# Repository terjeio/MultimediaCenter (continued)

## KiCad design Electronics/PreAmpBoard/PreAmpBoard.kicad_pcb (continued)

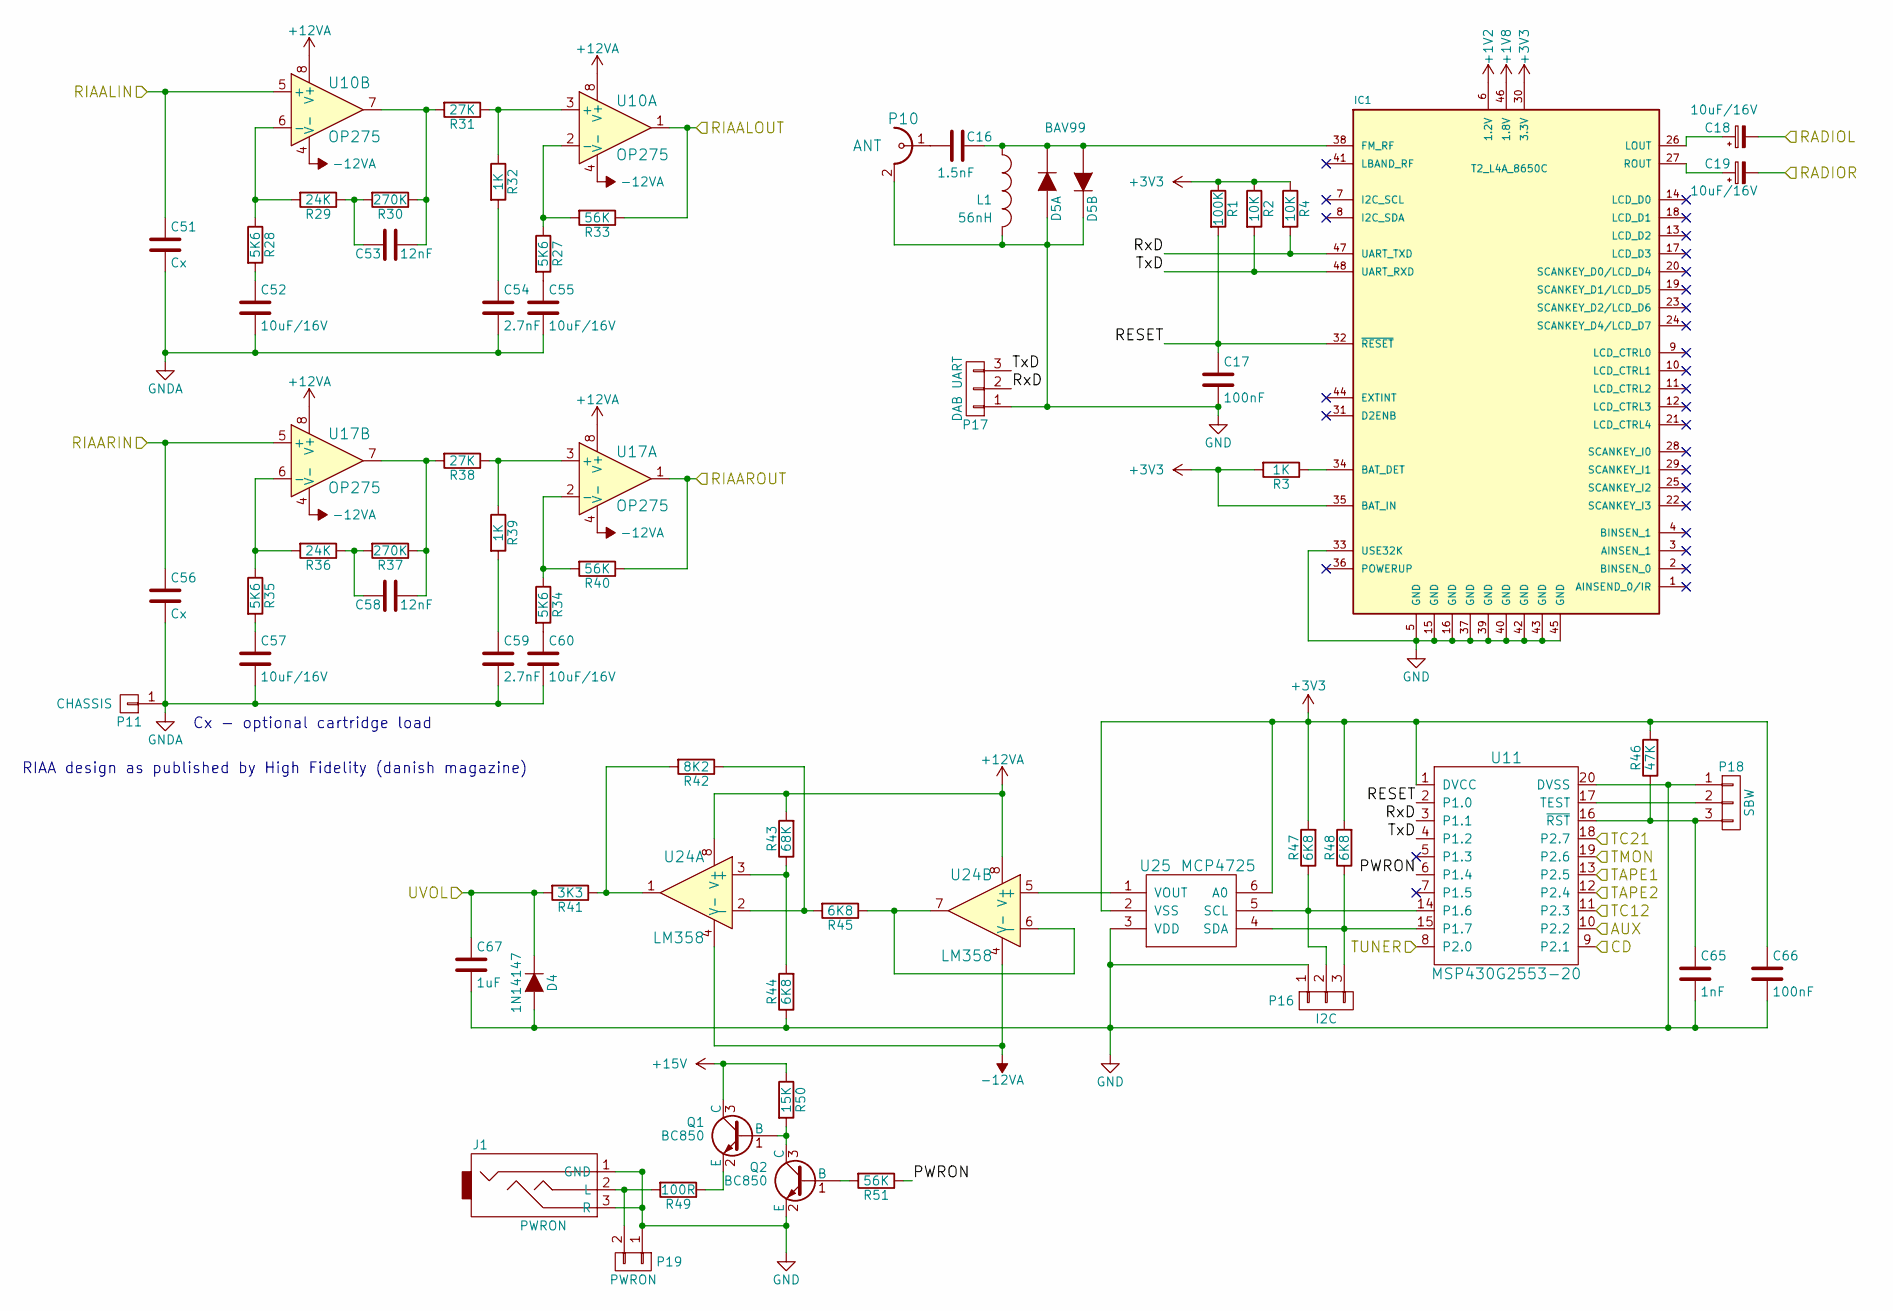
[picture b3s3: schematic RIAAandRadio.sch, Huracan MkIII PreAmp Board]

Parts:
C16: 1.5nF; C_0805
C17, C66: 100nF; C_1206
C18, C19: 10uF/16V; c_elec_3x5.3
C51, C56: Cx; C_Disc_D3_P5
C52, C55, C57, C60: 10uF/16V; C_Radial_D5_L11_P2.5
C53, C58: 12nF; C_Disc_D3_P5
C54, C59: 2.7nF; C_Disc_D3_P5
C65: 1nF; C_0805
C67: 1uF; C_1206
D4: 1N14147; SOD-123
D5: BAV99; SOT-23
IC1: T2_L4A_8650C; T2-L4A-8650C
J1: PWRON; PSG01538
L1: 56nH; R_0805
P10: ANT; CON-SMA-EDGE
P11: CHASSIS; Pin_Header_Straight_1x01
P16: I2C; 70543-03
P17: DAB UART; 70543-03
P18: SBW; Pin_Header_Straight_1x03
P19: PWRON; Pin_Header_Straight_1x02
Q1, Q2: BC850; SOT-23
R1: 100K; R_0805
R2, R4: 10K; R_0805
R3: 1K; R_0805
R27, R28, R34, R35: 5K6; Resistor_Horizontal_RM10mm
R29, R36: 24K; Resistor_Horizontal_RM10mm
R30, R37: 270K; Resistor_Horizontal_RM10mm
R31, R38: 27K; Resistor_Horizontal_RM10mm
R32, R39: 1K; Resistor_Horizontal_RM10mm
R33, R40: 56K; Resistor_Horizontal_RM10mm
R41: 3K3; R_0805
R42: 8K2; R_0805
R43: 68K; R_0805
R44, R45, R47, R48: 6K8; R_0805
R46: 47K; R_0805
R49: 100R; Resistor_Horizontal_RM10mm
R50: 15K; R_0805
R51: 56K; R_0805
U10, U17: OP275; DIP-8__300
U11: MSP430G2553-20; TSSOP20
U24: LM358; SO-8
U25: MCP4725; SOT23-6

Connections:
+1V2: IC1.6 (1.2V); also elsewhere on the board
+1V8: IC1.46 (1.8V); also elsewhere on the board
+3V3: C66.1, IC1.30 (3.3V), IC1.35 (BAT_IN), R1.1, R2.1, R3.2, R4.1, R46.2, R47.2, R48.2, U11.1 (DVCC), U25.2 (VSS), U25.6 (A0); also elsewhere on the board
+12VA: R43.2, U10.8 (V+), U17.8 (V+), U24.8 (V+); also elsewhere on the board
+15V: Q1.3 (C), R50.1
/AUX: U11.10 (P2.2); also elsewhere on the board
/CD: U11.9 (P2.1); also elsewhere on the board
/RADIOL: C18.2; also elsewhere on the board
/RADIOR: C19.2; also elsewhere on the board
/RIAA&Radio/PWRON: R51.1, U11.6 (P1.4)
/RIAA&Radio/RESET: C17.1, IC1.32 (~RESET), R1.2, U11.2 (P1.0)
/RIAA&Radio/RxD: IC1.47 (UART_TXD), P17.2, R4.2, U11.3 (P1.1)
/RIAA&Radio/TxD: IC1.48 (UART_RXD), P17.3, R2.2, U11.4 (P1.2)
/RIAALIN: C51.1, U10.5 (+); also elsewhere on the board
/RIAALOUT: R33.1, U10.1; also elsewhere on the board
/RIAARIN: C56.1, U17.5 (+); also elsewhere on the board
/RIAAROUT: R40.1, U17.1; also elsewhere on the board
/TAPE1: U11.13 (P2.5); also elsewhere on the board
/TAPE2: U11.12 (P2.4); also elsewhere on the board
/TC12: U11.11 (P2.3); also elsewhere on the board
/TC21: U11.18 (P2.7); also elsewhere on the board
/TMON: U11.19 (P2.6); also elsewhere on the board
/TUNER: U11.8 (P2.0); also elsewhere on the board
/VOLCTR: C67.1, D4.1 (K), R41.2; also elsewhere on the board
GND: C17.2, C51.2, C52.2, C54.2, C55.2, C56.2, C57.2, C59.2, C60.2, C65.2, C66.2, C67.2, D4.2 (A), D5.1 (A), D5.2 (K), IC1.5 (GND), IC1.15 (GND), IC1.16 (GND), IC1.33 (USE32K), IC1.37 (GND), IC1.39 (GND), IC1.40 (GND), IC1.42 (GND), IC1.43 (GND), IC1.45 (GND), J1.1 (GND), J1.3 (R), L1.2, P10.2, P11.1, P16.1, P17.1, P18.1, P19.1, Q2.2 (E), R44.1, U11.20 (DVSS), U25.3 (VDD); also elsewhere on the board
unnamed: C16.1, P10.1
unnamed: C16.2, D5.3 (K), IC1.38 (FM_RF), L1.1
unnamed: C18.1, IC1.26 (LOUT)
unnamed: C19.1, IC1.27 (ROUT)
unnamed: C52.1, R28.2
unnamed: C53.1, R30.1, R31.2, U10.7
unnamed: C53.2, R29.1, R30.2
unnamed: C54.1, R32.2
unnamed: C55.1, R27.2
unnamed: C57.1, R35.2
unnamed: C58.1, R37.1, R38.2, U17.7
unnamed: C58.2, R36.1, R37.2
unnamed: C59.1, R39.2
unnamed: C60.1, R34.2
unnamed: C65.1, P18.3, R46.1, U11.16 (~RST~)
unnamed: IC1.34 (BAT_DET), R3.1
unnamed: J1.2 (L), P19.2, R49.2
unnamed: P16.2, R47.1, U11.14 (P1.6), U25.5 (SCL)
unnamed: P16.3, R48.1, U11.15 (P1.7), U25.4 (SDA)
unnamed: P18.2, U11.17 (TEST)
unnamed: Q1.1 (B), Q2.3 (C), R50.2
unnamed: Q1.2 (E), R49.1
unnamed: Q2.1 (B), R51.2
unnamed: R27.1, R33.2, U10.2 (-)
unnamed: R28.1, R29.2, U10.6 (-)
unnamed: R31.1, R32.1, U10.3 (+)
unnamed: R34.1, R40.2, U17.2 (-)
unnamed: R35.1, R36.2, U17.6 (-)
unnamed: R38.1, R39.1, U17.3 (+)
unnamed: R41.1, R42.2, U24.1
unnamed: R42.1, R45.2, U24.2 (-)
unnamed: R43.1, R44.2, U24.3 (+)
unnamed: R45.1, U24.6 (-), U24.7
unnamed: U24.5 (+), U25.1 (VOUT)

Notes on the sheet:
Cx - optional cartridge load
RIAA design as published by High Fidelity (danish magazine)

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
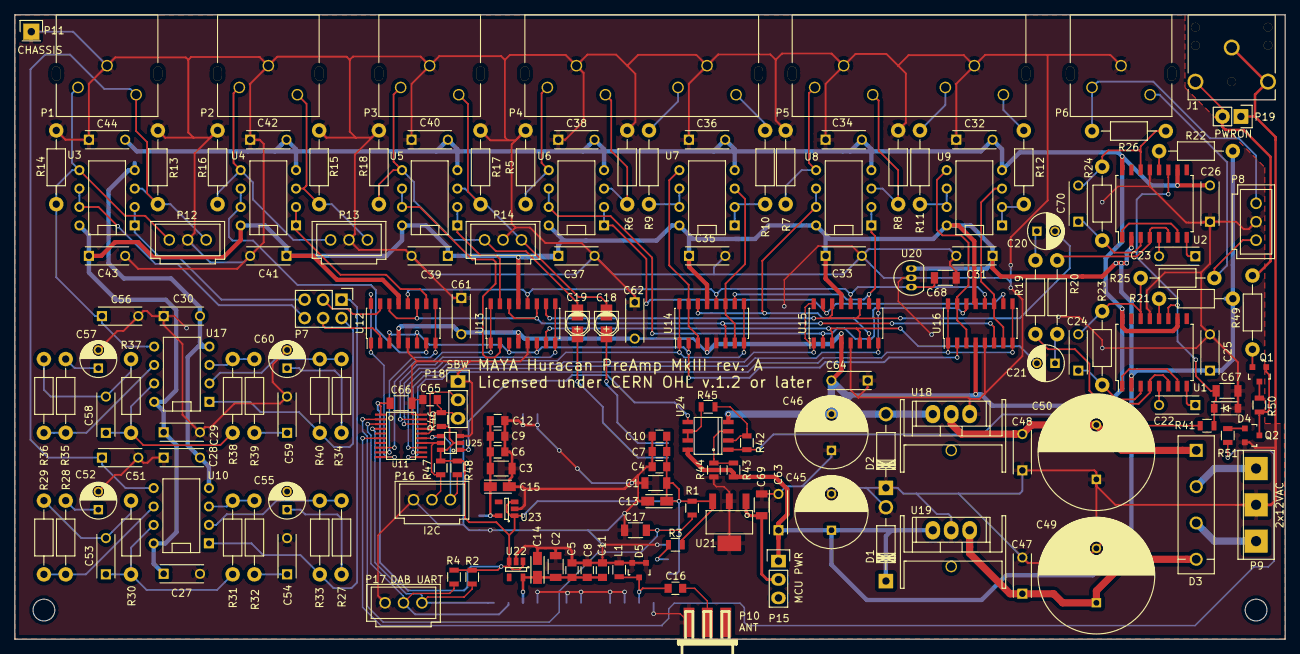
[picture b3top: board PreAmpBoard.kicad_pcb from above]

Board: 2 copper layers, 175.0 x 86.0 mm, 175 parts (1 on the bottom side), 118 nets.

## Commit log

2017-09-18 :confetti_ball: Added .gitattributes & .gitignore files
2017-09-18 Initial commit of first part of design
2017-09-18 updated readme files
2017-09-19 Added code for Raspberry Pi power handling
    A Raspberry Pi daemon for power handling, to be used together with the
    power switch.
2017-09-19 Added PowerSwitch firmware
2017-09-19 Added build files
2017-09-20 Added reference to pre-amp board firmware, moved power switch firmwre
2017-09-20 Added controller schematics and PCB
